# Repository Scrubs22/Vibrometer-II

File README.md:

> ⚠️ **Status: Work in Progress (WIP)**  
> This project is actively being developed and is currently in the development phase. The hardware schematics, 3D enclosures, and firmware files are subject to frequent changes until a complete, fully tested working prototype is validated. Use with caution!

# Vibrometer-II

Vibrometer-II is an advanced, high-performance upgrade to my original vibration monitor project. 

## The Evolution: Upgrading to RP2040

The previous version relied on an **ATmega328-P** architecture powered by twin CR2032 cells. While functional, it suffered from a bulky form factor, increased mass, and inherent measurement inaccuracies. 

To overcome these constraints, **Vibrometer-II** implements a much cleaner and faster **Raspberry Pi RP2040** core. This hardware migration achieves:
* **Drastic Form Factor Reduction:** Minimizes overall mass and physical device footprint.
* **Enhanced Measurement Accuracy:** Delivers faster data capture and processing speeds.
* **Custom Enclosure:** A brand-new structural enclosure tailored explicitly for the onboard sensor.
* **Dual-Tier UI Ecosystem:** Features advanced and basic user interfaces engineered for both high-level control and low-level system implementation.

## Technical Specifications: 

The **Vibrometer-II** uses the *LSM6DS3* as its main IMU, and the *RP2040* as the MCU. For memory, two *MX25L3233FM1* each featuring 4MB or storage.

### Individual Specifications:

#### LSM6DS3:
* Manufactured by STMicrocontrollers
* Sensor Type: 3-axis accelerometer and 3-axis gyroscope combo (6-axis IMU)
* Accelerometer Full-Scale Range: ±2 / ±4 / ±8 / ±16 g
* Gyroscope Full-Scale Range: ±125 / ±245 / ±500 / ±1000 / ±2000 dps (degrees per second)
* Power Consumption:
    * 0.9 mA in combo normal mode
	* 1.25 mA in high-performance mode (up to 1.6 kHz ODR)
	* 6 μA in power-down mode
* Supply Voltage:
    * Analog supply: 1.71V to 3.6V
	* IO supply: 1.62V
* Interface Options: SPI and I²C serial interfaces with a main processor data synchronization feature

#### RP2040:

* Manufactured by Raspberry Pi Ltd
* Core Architecture: Dual-core ARM Cortex-M0+
* Clock Frequency: Variable, running up to 133 MHz
* Internal Memory: 264 KB of on-chip SRAM divided into 6 independent banks
* External Flash Support: QSPI interface supporting up to 16 MB of external flash memory with Execute-in-Place (XIP) capabilities
* Peripherals & I/O:
	* 30 multi-function GPIO pins (26 exposed on the Pico standard form factor)
	* 2 × UART, 2 × SPI, and 2 × I2C controllers
	* 16 × PWM channels
	* 4-channel 12-bit SAR Analog-to-Digital Converter (ADC) with an integrated internal temperature sensor
* Unique Feature: 8 × Programmable I/O (PIO) state machines used to create customized hardware peripheral interfaces
* USB Interface: USB 1.1 controller supporting both Host and Device operations
* Package Options: 56-pin QFN package measuring 7×7 mm

#### MXL25L3233FM1:

* Manufacturer: Macronix International Co., Ltd.
* Memory Type: Serial Multi-I/O (MXSMIO®) CMOS NOR Flash
* Density / Capacity: 32 Megabits (Mbit), which translates to 4 Megabytes (MB)
* Interface Protocol: Serial Peripheral Interface (SPI) supporting Mode 0 and Mode 3
* I/O Width Configurations: Standard SPI (x1 I/O), Dual SPI (x2 I/O), and Quad SPI (x4 I/O) configurations
* Maximum Clock Frequency: 133 MHz
* Operating Voltage Range: 2.65V to 3.6V
* Memory Architecture:
	* 1,024 equal sectors (4 KB each)
	* 128 equal blocks (32 KB each)
	* 64 equal blocks (64 KB each)
* Standout Performance: Supports Performance Enhance Mode / Execute-in-Place (XIP) to read data without command overhead
* Operating Temperature: Industrial grade protection rating from -40°C to +85°C
* Package Form Factor: 8-pin SOP (Small Outline Package) / 8-SOIC

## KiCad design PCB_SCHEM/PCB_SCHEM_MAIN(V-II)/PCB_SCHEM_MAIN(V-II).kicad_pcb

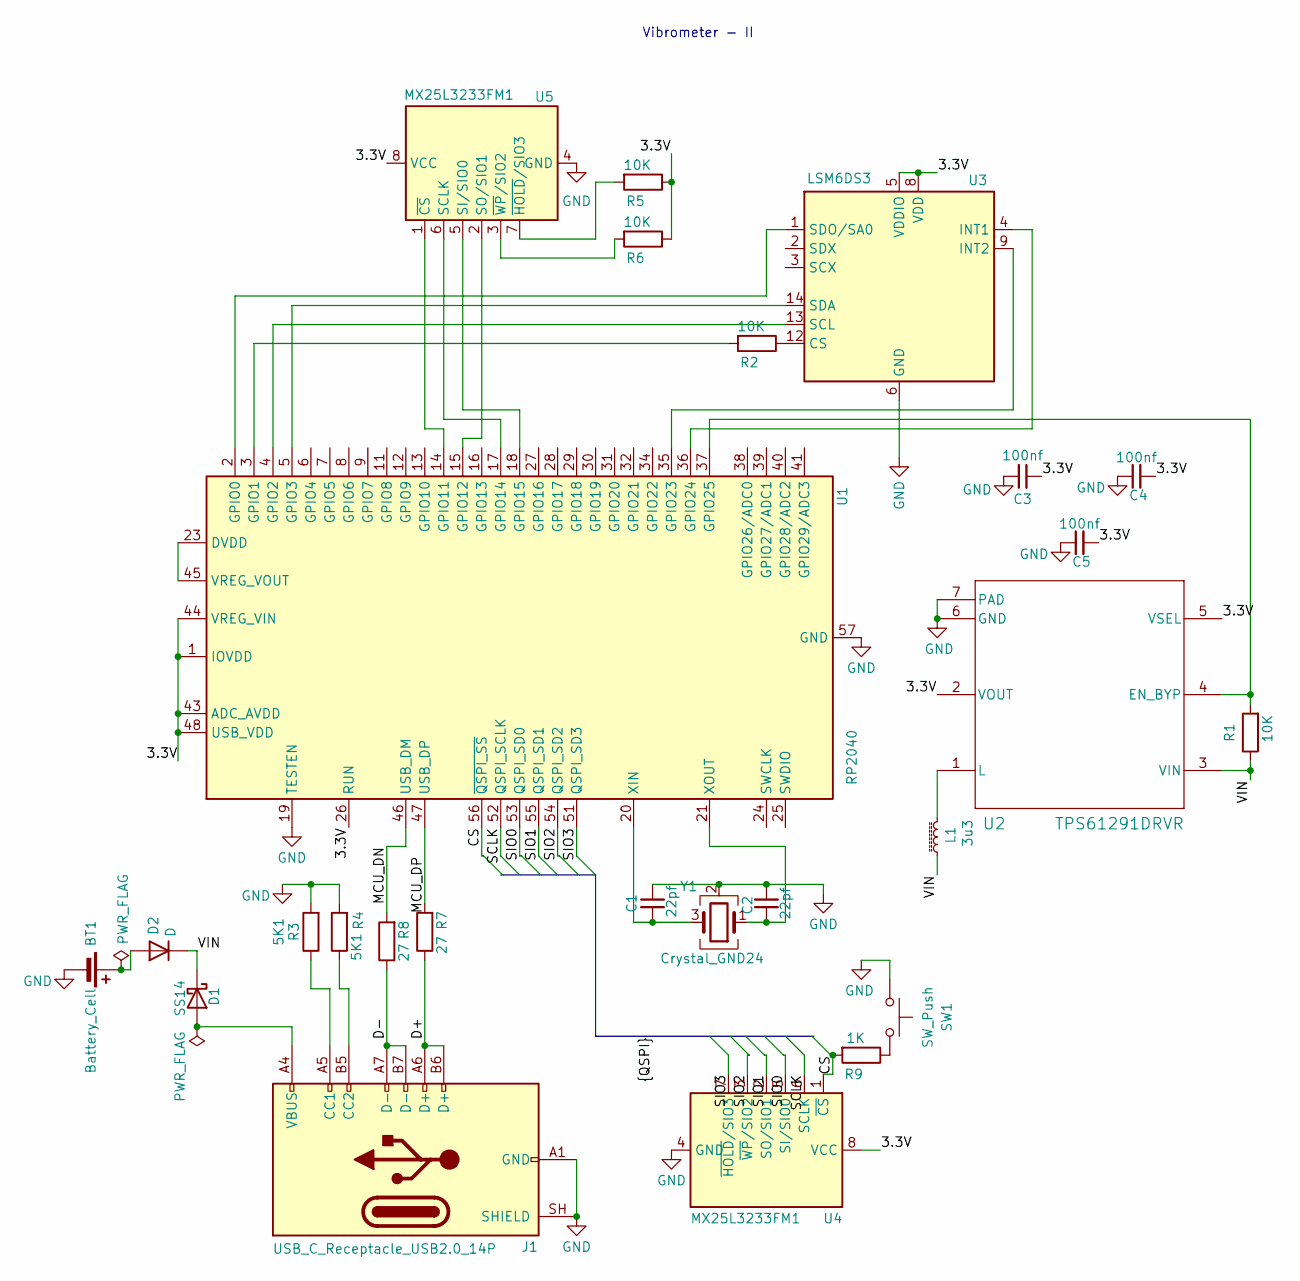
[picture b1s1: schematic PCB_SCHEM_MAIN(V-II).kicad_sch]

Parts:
BT1: Battery_Cell; BatteryHolder_MYOUNG_BS-07-A1BJ001_CR2032
C1, C2: 22pf; C_0603_1608Metric_Pad1.08x0.95mm_HandSolder
C3, C4, C5: 100nf; C_0603_1608Metric_Pad1.08x0.95mm_HandSolder
D1: SS14; D_SMA
D2: D; D_SMA
J1: USB_C_Receptacle_USB2.0_14P; USB_C_Receptacle_GCT_USB4105-xx-A_16P_TopMnt_Horizontal
L1: 3u3; L_Coilcraft_LPS3010
R1, R2, R5, R6: 10K; R_0603_1608Metric_Pad0.98x0.95mm_HandSolder
R3, R4: 5K1; R_0603_1608Metric_Pad0.98x0.95mm_HandSolder
R7, R8: 27; R_0603_1608Metric_Pad0.98x0.95mm_HandSolder
R9: 1K; R_0603_1608Metric_Pad0.98x0.95mm_HandSolder
SW1: SW_Push; SW_SPST_EVQP2_MiddlePushTravel_H2.5mm
U1: RP2040; QFN-56-1EP_7x7mm_P0.4mm_EP3.2x3.2mm
U2: TPS61291DRVR; WSON-6-1EP_2x2mm_P0.65mm_EP1x1.6mm
U3: LSM6DS3; LGA-14_3x2.5mm_P0.5mm_LayoutBorder3x4y
U4, U5: MX25L3233FM1; JEITA_SOIC-8_3.9x4.9mm_P1.27mm
Y1: Crystal_GND24; Crystal_SMD_Abracon_ABM8AIG-4Pin_3.2x2.5mm

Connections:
/3.3V: C3.2, C4.1, C5.1, R5.1, R6.1, U1.1 (IOVDD), U1.10 (IOVDD), U1.22 (IOVDD), U1.26 (RUN), U1.33 (IOVDD), U1.42 (IOVDD), U1.43 (ADC_AVDD), U1.44 (VREG_VIN), U1.48 (USB_VDD), U1.49 (IOVDD), U2.2 (VOUT), U2.5 (VSEL), U3.5 (VDDIO), U3.8 (VDD), U4.8 (VCC), U5.8 (VCC)
/CS: R9.2, U1.56 (~QSPI_SS), U4.1 (~CS)
/D+: J1.A6 (D+), J1.B6 (D+), R7.1
/D-: J1.A7 (D-), J1.B7 (D-), R8.1
/MCU_DN: R8.2, U1.46 (USB_DM)
/MCU_DP: R7.2, U1.47 (USB_DP)
/SCLK: U1.52 (QSPI_SCLK), U4.6 (SCLK)
/SIO0: U1.53 (QSPI_SD0), U4.5 (SI/SIO0)
/SIO1: U1.55 (QSPI_SD1), U4.2 (SO/SIO1)
/SIO2: U1.54 (QSPI_SD2), U4.3 (~WP/SIO2)
/SIO3: U1.51 (QSPI_SD3), U4.7 (~HOLD/SIO3)
/VIN: D1.1 (K), D2.1 (K), L1.1, R1.1, U2.3 (VIN)
GND: BT1.2 (-), C1.2, C2.2, C3.1, C4.2, C5.2, J1.A1 (GND), J1.A12 (GND), J1.B1 (GND), J1.B12 (GND), J1.SH (SHIELD), R3.2, R4.2, SW1.1, U1.19 (TESTEN), U1.57 (GND), U2.6 (GND), U2.7 (PAD), U3.6 (GND), U3.7 (GND), U4.4 (GND), U5.4 (GND), Y1.2 (G), Y1.4 (G)
unnamed: BT1.1 (+), D2.2 (A)
unnamed: D1.2 (A), J1.A4 (VBUS), J1.A9 (VBUS), J1.B4 (VBUS), J1.B9 (VBUS)
unnamed: J1.A5 (CC1), R3.1
unnamed: J1.B5 (CC2), R4.1
unnamed: R9.1, SW1.2
unnamed: U1.2 (GPIO0), U3.1 (SDO/SA0)
unnamed: R2.2, U1.3 (GPIO1)
unnamed: U1.4 (GPIO2), U3.13 (SCL)
unnamed: U1.5 (GPIO3), U3.14 (SDA)
unnamed: U1.14 (GPIO11), U5.1 (~CS)
unnamed: U1.15 (GPIO12), U5.2 (SO/SIO1)
unnamed: U1.17 (GPIO14), U5.6 (SCLK)
unnamed: U1.18 (GPIO15), U5.5 (SI/SIO0)
unnamed: U1.35 (GPIO23), U3.9 (INT2)
unnamed: U1.36 (GPIO24), U3.4 (INT1)
unnamed: R1.2, U1.37 (GPIO25), U2.4 (EN_BYP)
unnamed: U1.23 (DVDD), U1.45 (VREG_VOUT), U1.50 (DVDD)
unnamed: C1.1, U1.20 (XIN), Y1.3
unnamed: C2.1, U1.21 (XOUT), Y1.1
unnamed: L1.2, U2.1 (L)
unnamed: R2.1, U3.12 (CS)
unnamed: R5.2, U5.7 (~HOLD/SIO3)
unnamed: R6.2, U5.3 (~WP/SIO2)

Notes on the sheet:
Vibrometer - II

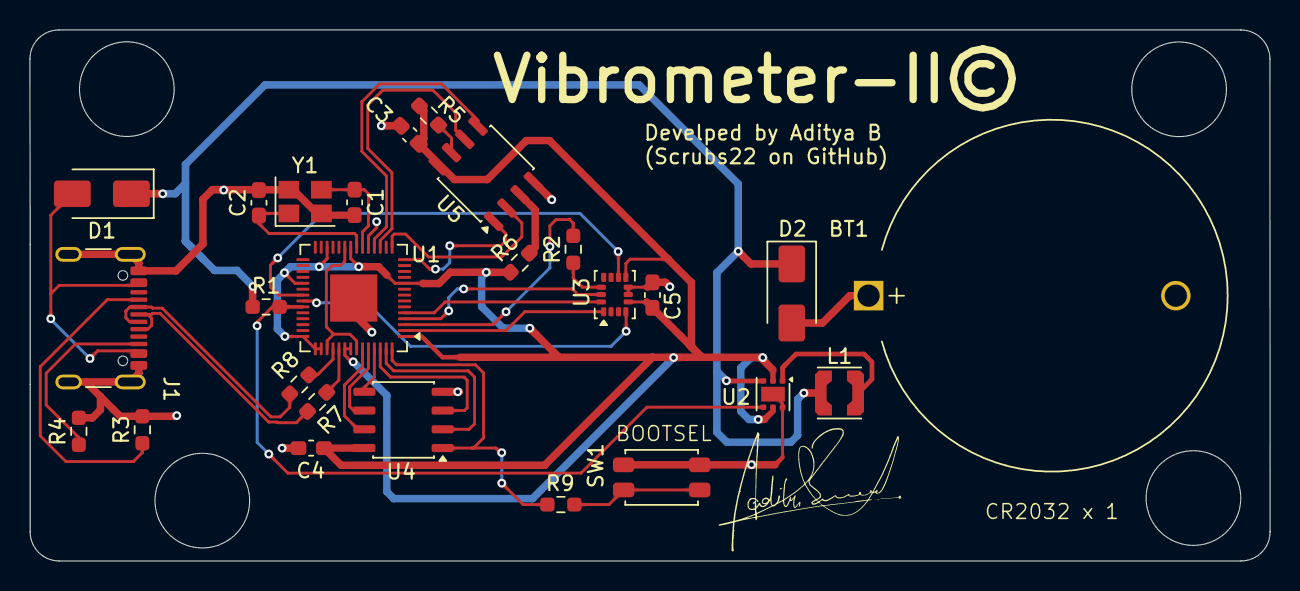
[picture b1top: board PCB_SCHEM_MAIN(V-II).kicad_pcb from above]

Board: 2 copper layers, 84.0 x 36.0 mm, 26 parts (0 on the bottom side), 36 nets.
